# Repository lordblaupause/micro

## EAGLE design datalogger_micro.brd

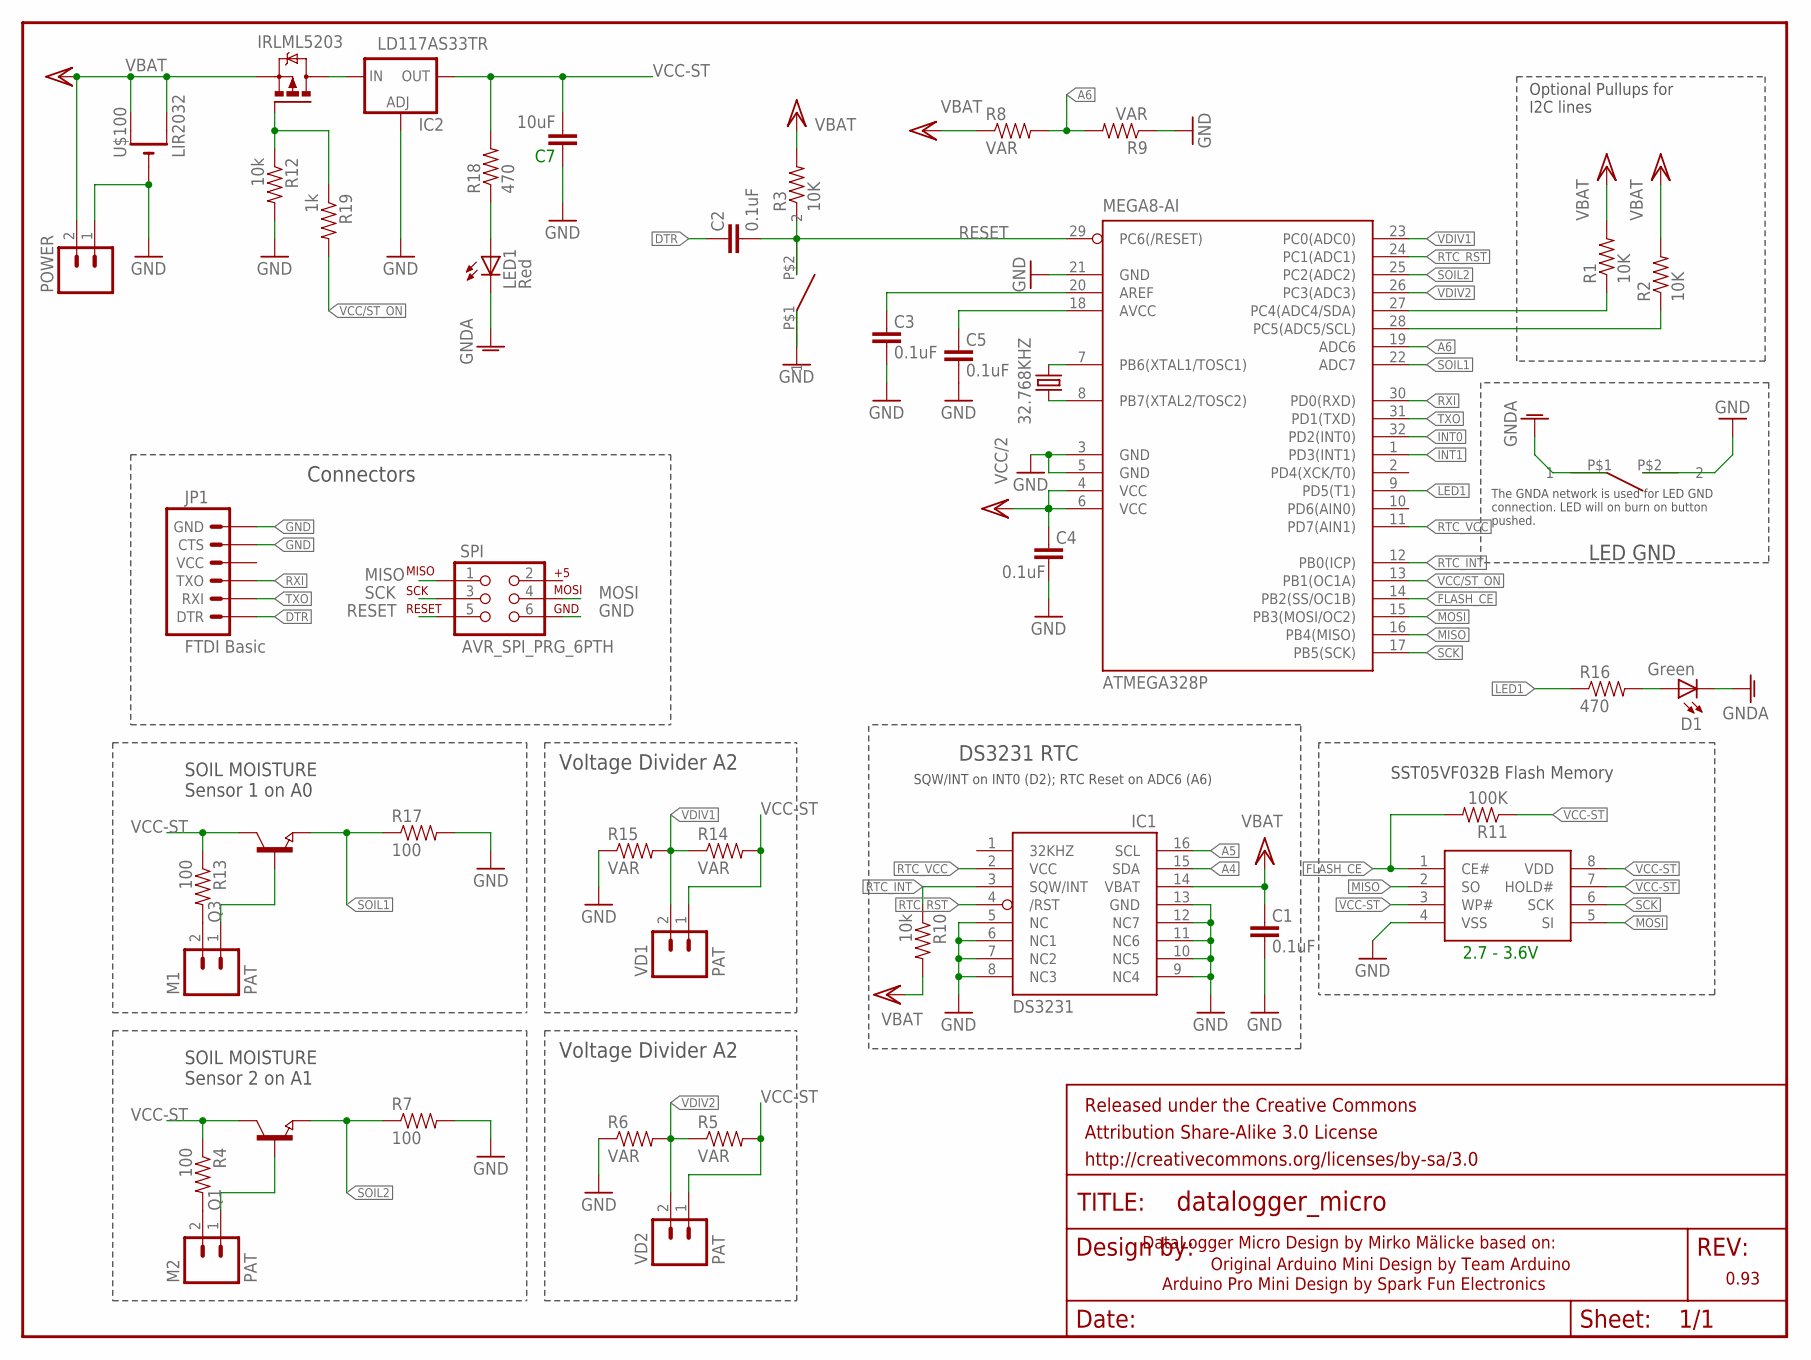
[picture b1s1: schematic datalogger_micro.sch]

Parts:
32.768KHZ: CRYSTALTC38H; TC38H
ATMEGA328P: MEGA8-AI; TQFP32-08
C1, C2, C3, C4, C5: 0.1uF; 0603-CAP
C7: 10uF; 1206
D1: Green; 0603-LED-ALT1
FRAME1: FRAME-LETTER; CREATIVE_COMMONS
IC1: DS3231/SO; SO16W
IC2: LD117AS33TR; SOT223
JP1: FTDI Basic; 1X06
LED1: Red; 0603-LED-ALT1
M1, M2: PAT; 1X02
POWER: M02PTH; 1X02
Q1, Q3: NPN-TRANSISTOR_SOT23; SOT23
Q2: IRLML5203; MICRO3
R1, R2, R3: 10K; 0603-RES
R4, R7, R13, R17: 100; 0603-RES
R5, R6, R8, R9, R14, R15: VAR; 0603-RES
R10, R12: 10k; 0603-RES
R11: 100K; 0603-RES
R16, R18: 470; 0603-RES
R19: 1k; 0603-RES
SPI: AVR_SPI_PRG_6PTH; 2X3
U$1, U$2: DRUCKTASTER-1PIN
U$3: SST25VF032B; SO-08
U$100: LIR2032; CR2032-SMD
VD1, VD2: PAT; 1X02

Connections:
A4: ATMEGA328P.27 (PC4(ADC4/SDA)), IC1.15 (SDA), R1.1
A5: ATMEGA328P.28 (PC5(ADC5/SCL)), IC1.16 (SCL), R2.1
A6: ATMEGA328P.19 (ADC6), R8.2, R9.2
DTR: C2.2, JP1.1 (DTR)
FLASH_CE: ATMEGA328P.14 (PB2(SS/OC1B)), R11.2, U$3.1 (CE#)
GND: ATMEGA328P.3 (GND), ATMEGA328P.5 (GND), ATMEGA328P.21 (GND), C1.1, C3.1, C4.1, C5.1, C7.2, IC1.5 (NC), IC1.6 (NC1), IC1.7 (NC2), IC1.8 (NC3), IC1.9 (NC4), IC1.10 (NC5), IC1.11 (NC6), IC1.12 (NC7), IC1.13 (GND), IC2.1 (ADJ), JP1.5 (CTS), JP1.6 (GND), POWER.1, R6.1, R7.2, R9.1, R12.2, R15.1, R17.2, SPI.6, U$1.P$1 (1), U$2.P$2 (2), U$3.4 (VSS), U$100.-
GNDA: D1.C, LED1.C, U$2.P$1 (1)
INT0: ATMEGA328P.32 (PD2(INT0))
INT1: ATMEGA328P.1 (PD3(INT1))
LED1: ATMEGA328P.9 (PD5(T1)), R16.1
MISO: ATMEGA328P.16 (PB4(MISO)), SPI.1, U$3.2 (SO)
MOSI: ATMEGA328P.15 (PB3(MOSI/OC2)), SPI.4, U$3.5 (SI)
unnamed: ATMEGA328P.20 (AREF), C3.2
unnamed: 32.768KHZ.1, ATMEGA328P.7 (PB6(XTAL1/TOSC1))
unnamed: 32.768KHZ.2, ATMEGA328P.8 (PB7(XTAL2/TOSC2))
unnamed: LED1.A, R18.1
unnamed: M2.1, Q1.1 (B)
unnamed: M1.1, Q3.1 (B)
unnamed: D1.A, R16.2
unnamed: M2.2, R4.2
unnamed: M1.2, R13.2
unnamed: IC2.3 (IN), Q2.3 (D)
unnamed: Q2.1 (G), R12.1, R19.1
RESET: ATMEGA328P.29 (PC6(/RESET)), C2.1, R3.1, SPI.5, U$1.P$2 (2)
RTC_INT: ATMEGA328P.12 (PB0(ICP)), IC1.3 (SQW/INT), R10.1
RTC_RST: ATMEGA328P.24 (PC1(ADC1)), IC1.4 (/RST)
RTC_VCC: ATMEGA328P.11 (PD7(AIN1)), IC1.2 (VCC)
RXI: ATMEGA328P.30 (PD0(RXD)), JP1.3 (TXO)
SCK: ATMEGA328P.17 (PB5(SCK)), SPI.3, U$3.6 (SCK)
SOIL1: ATMEGA328P.22 (ADC7), Q3.2 (E), R17.1
SOIL2: ATMEGA328P.25 (PC2(ADC2)), Q1.2 (E), R7.1
TXO: ATMEGA328P.31 (PD1(TXD)), JP1.2 (RXI)
VBAT: ATMEGA328P.4 (VCC), ATMEGA328P.6 (VCC), ATMEGA328P.18 (AVCC), C1.2, C4.2, C5.2, IC1.14 (VBAT), POWER.2, Q2.2 (S), R1.2, R2.2, R3.2, R8.1, R10.2, U$100.+$1 (+), U$100.+$2 (+1)
VCC-ST: C7.1, IC2.2 (OUT), Q1.3 (C), Q3.3 (C), R4.1, R5.2, R11.1, R13.1, R14.2, R18.2, U$3.3 (WP#), U$3.7 (HOLD#), U$3.8 (VDD), VD1.1, VD2.1
VCC/ST_ON: ATMEGA328P.13 (PB1(OC1A)), R19.2
VDIV1: ATMEGA328P.23 (PC0(ADC0)), R14.1, R15.2, VD1.2
VDIV2: ATMEGA328P.26 (PC3(ADC3)), R5.1, R6.2, VD2.2

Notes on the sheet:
Original Arduino Mini Design by Team Arduino
Arduino Pro Mini Design by Spark Fun Electronics
Optional Pullups for I2C lines
0.93
SST05VF032B Flash Memory
DataLogger Micro Design by Mirko Mälicke based on:
DS3231 RTC
SQW/INT on INT0 (D2); RTC Reset on ADC6 (A6)
LED GND
The GNDA network is used for LED GND connection. LED will on burn on button pushed.
SOIL MOISTURE Sensor 1 on A0
SOIL MOISTURE Sensor 2 on A1
Voltage Divider A2
2.7 - 3.6V
Connectors

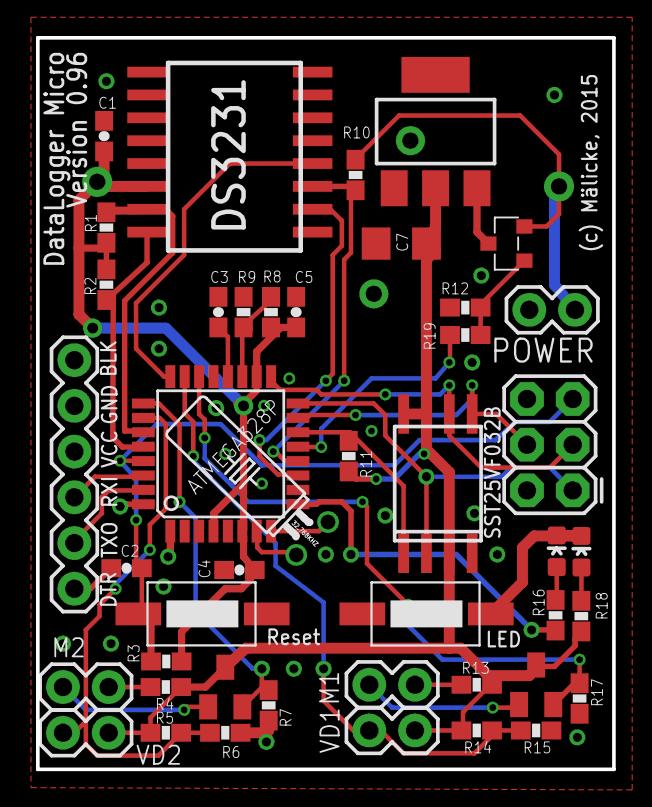
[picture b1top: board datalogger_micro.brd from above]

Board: 2 copper layers, 32.0 x 40.6 mm, 46 parts (1 on the bottom side), 35 nets.

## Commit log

2015-04-13 :lollipop: Added .gitattributes & .gitignore files
2015-04-13 Version 0.93
    Printed Verison.
    Komplete Layout Rework. Using 0603 LED, CAP and RES.
    Replaced ATMega328-AU by ATMEGA328P BIP-28 Version
2015-05-05 v0.93 label fix
    Some labels on the layout were removed. No functional changes.
2015-05-21 v0.93 label position fix
    some resistor label positions were fixed
2015-06-23 version 0.94
    first draft of 0.94, not the printed one.
    integrates the LD117 voltage regulator
2015-07-16 schematic rework for 0.95
    Schematic rework for 0.95 version. Not productive, no layout.
2015-07-17 layout rework
    Still need to include the battery, maybe replace LM117
2015-07-17 same as last
    another variant of LIR2450
2015-07-18 one-sided
    moved layout to one sided again, use SMT battery pack.
2015-07-19 schematic adaptions
    a lot of schematic adaptions. included various C and Rs were neceassary.
    MOSFET instead of Transistor on LM1117..
2015-07-20 schematics finalized
    schematics are finalized and will be verified
2015-07-20 .pro files included for sync reasons
2015-07-20 routing
    Routing is 90% complete
2015-07-21 bug fix
2015-07-21 pre 0.95
    Board finalized. Will be printed after last quality check.
2015-07-22 bug fix
    A0 had no connection to sensor
2015-07-22 sync release
    GIT crashed synced last .brd only partially. (No idea why?!?!?!) re-sync
    with wrong A0, then sync changed A0....
2015-07-22 A0 bug fix
    re commit, first was damageded by GIT. included <<<< HEAD into the file
2015-07-22 drill size
    found one via < 0.3
2015-07-24 VERSION 0.95
    finalized Version 0.95, to be printed
2015-07-24 bugfix
    removed a uneccessary connection
2015-07-27 VERSION 0.95 final
    final printed Version 0.95 to be published
2015-07-27 bugfix
    LAST MINUTE clearance bugfix
2015-07-28 layout error bugfixes
2015-08-21 MOSFET fix
2015-08-24 SST25 Layout
    pins 5-8 were switched
2015-08-25 VCC-ST active low
    VCC ST is now active low by p channel mosfet
2015-08-26 layout fixes
2015-08-27 v0.96 Prototype
2015-08-27 C6 out

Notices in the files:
parts and their libraries:
SparkFun-Aesthetics: Licensing: CC v3.0 Share-Alike You are welcome to use this library for commercial purposes.
SparkFun-Aesthetics: Released under the Creative Commons Attribution Share-Alike 3.0 License
SparkFun-Aesthetics: http://creativecommons.org/licenses/by-sa/3.0
